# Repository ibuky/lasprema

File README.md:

# Avion
An wing-like 53-key keyboard inspired by Atreus.

### Features
- has 53 keys.
- is column-staggered.
- Supports Kailh choc and Cherry MX and its compatibles.
- has a central display spot for an artisan keycap.

[More information is available here.](https://www.taneyats.com/entry/lets-see-my-avion)(Japanese)

### Beta Version
This project still have lots to be completed.

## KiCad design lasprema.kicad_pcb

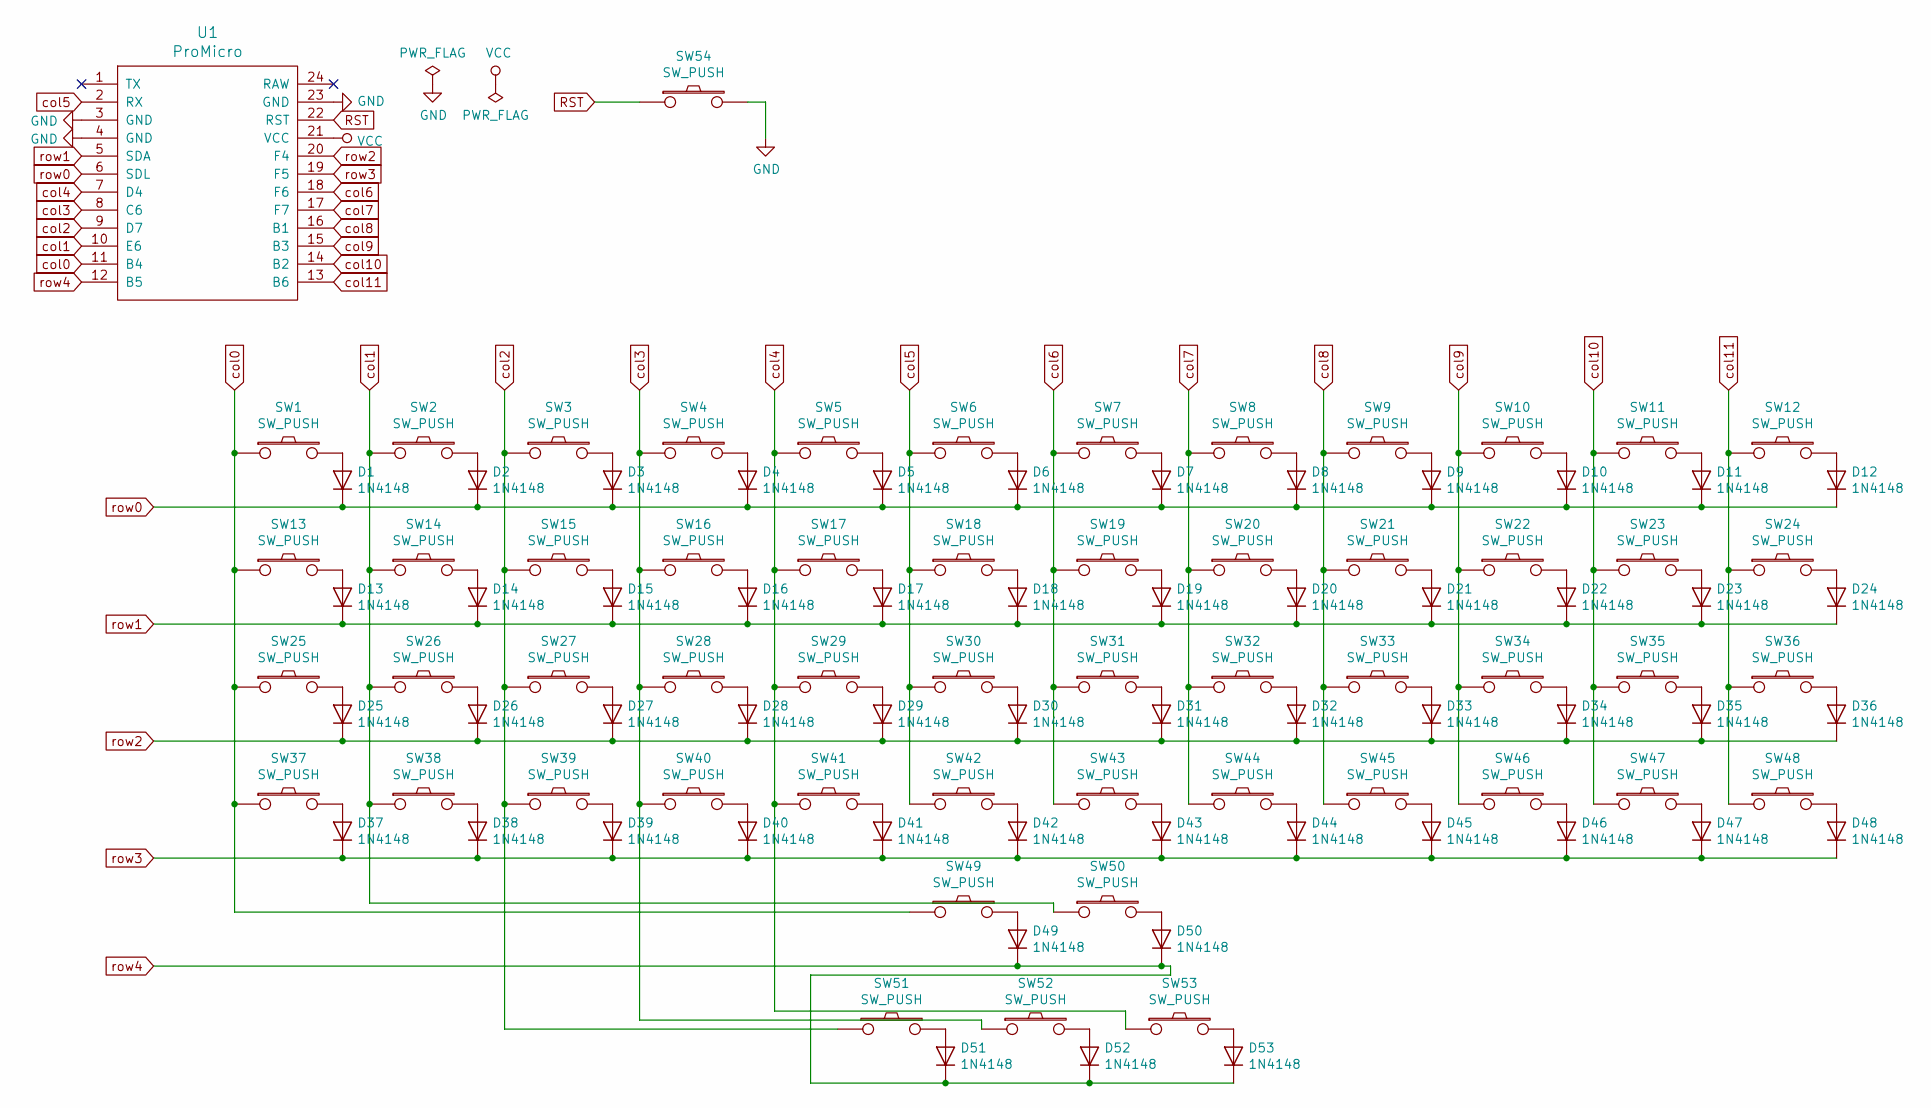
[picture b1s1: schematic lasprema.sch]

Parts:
D1, D2, D3, D4, D5, D6, D7, D8, D9, D10, D11, D12, D13, D14, D15, D16, D17, D18, D19, D20, D21, D22, D23, D24, D25, D26, D27, D28, D29, D30, D31, D32, D33, D34, D35, D36, D37, D38, D39, D40, D41, D42, D43, D44, D45, D46, D47, D48, D49, D50, D51, D52, D53: 1N4148; D_DO-35_SOD27_P7.62mm_Horizontal
SW1, SW2, SW3, SW4, SW5, SW6, SW7, SW8, SW9, SW10, SW11, SW12, SW13, SW14, SW15, SW16, SW17, SW18, SW19, SW20, SW21, SW22, SW23, SW24, SW25, SW26, SW27, SW28, SW29, SW30, SW31, SW32, SW33, SW34, SW35, SW36, SW37, SW38, SW39, SW40, SW41, SW42, SW43, SW44, SW45, SW46, SW47, SW48, SW49, SW50, SW51, SW52, SW53: SW_PUSH; lopro_compatible
SW54: SW_PUSH; SW_PUSH_6mm
U1: ProMicro

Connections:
GND: SW54.2, U1.3 (GND), U1.4 (GND), U1.23 (GND)
unnamed: D1.2 (A), SW1.2
unnamed: D2.2 (A), SW2.2
unnamed: D3.2 (A), SW3.2
unnamed: D4.2 (A), SW4.2
unnamed: D5.2 (A), SW5.2
unnamed: D6.2 (A), SW6.2
unnamed: D7.2 (A), SW7.2
unnamed: D8.2 (A), SW8.2
unnamed: D9.2 (A), SW9.2
unnamed: D10.2 (A), SW10.2
unnamed: D11.2 (A), SW11.2
unnamed: D12.2 (A), SW12.2
unnamed: D13.2 (A), SW13.2
unnamed: D14.2 (A), SW14.2
unnamed: D15.2 (A), SW15.2
unnamed: D16.2 (A), SW16.2
unnamed: D17.2 (A), SW17.2
unnamed: D18.2 (A), SW18.2
unnamed: D19.2 (A), SW19.2
unnamed: D20.2 (A), SW20.2
unnamed: D21.2 (A), SW21.2
unnamed: D22.2 (A), SW22.2
unnamed: D23.2 (A), SW23.2
unnamed: D24.2 (A), SW24.2
unnamed: D25.2 (A), SW25.2
unnamed: D26.2 (A), SW26.2
unnamed: D27.2 (A), SW27.2
unnamed: D28.2 (A), SW28.2
unnamed: D29.2 (A), SW29.2
unnamed: D30.2 (A), SW30.2
unnamed: D31.2 (A), SW31.2
unnamed: D32.2 (A), SW32.2
unnamed: D33.2 (A), SW33.2
unnamed: D34.2 (A), SW34.2
unnamed: D35.2 (A), SW35.2
unnamed: D36.2 (A), SW36.2
unnamed: D37.2 (A), SW37.2
unnamed: D38.2 (A), SW38.2
unnamed: D39.2 (A), SW39.2
unnamed: D40.2 (A), SW40.2
unnamed: D41.2 (A), SW41.2
unnamed: D42.2 (A), SW42.2
unnamed: D43.2 (A), SW43.2
unnamed: D44.2 (A), SW44.2
unnamed: D45.2 (A), SW45.2
unnamed: D46.2 (A), SW46.2
unnamed: D47.2 (A), SW47.2
unnamed: D48.2 (A), SW48.2
unnamed: D49.2 (A), SW49.2
unnamed: D50.2 (A), SW50.2
unnamed: D51.2 (A), SW51.2
unnamed: D52.2 (A), SW52.2
unnamed: D53.2 (A), SW53.2
RST: SW54.1, U1.22 (RST)
VCC: U1.21 (VCC)
col0: SW1.1, SW13.1, SW25.1, SW37.1, SW49.1, U1.11 (B4)
col1: SW2.1, SW14.1, SW26.1, SW38.1, SW50.1, U1.10 (E6)
col2: SW3.1, SW15.1, SW27.1, SW39.1, SW51.1, U1.9 (D7)
col3: SW4.1, SW16.1, SW28.1, SW40.1, SW52.1, U1.8 (C6)
col4: SW5.1, SW17.1, SW29.1, SW41.1, SW53.1, U1.7 (D4)
col5: SW6.1, SW18.1, SW30.1, SW42.1, U1.2 (RX)
col6: SW7.1, SW19.1, SW31.1, SW43.1, U1.18 (F6)
col7: SW8.1, SW20.1, SW32.1, SW44.1, U1.17 (F7)
col8: SW9.1, SW21.1, SW33.1, SW45.1, U1.16 (B1)
col9: SW10.1, SW22.1, SW34.1, SW46.1, U1.15 (B3)
col10: SW11.1, SW23.1, SW35.1, SW47.1, U1.14 (B2)
col11: SW12.1, SW24.1, SW36.1, SW48.1, U1.13 (B6)
row0: D1.1 (K), D2.1 (K), D3.1 (K), D4.1 (K), D5.1 (K), D6.1 (K), D7.1 (K), D8.1 (K), D9.1 (K), D10.1 (K), D11.1 (K), D12.1 (K), U1.6 (SDL)
row1: D13.1 (K), D14.1 (K), D15.1 (K), D16.1 (K), D17.1 (K), D18.1 (K), D19.1 (K), D20.1 (K), D21.1 (K), D22.1 (K), D23.1 (K), D24.1 (K), U1.5 (SDA)
row2: D25.1 (K), D26.1 (K), D27.1 (K), D28.1 (K), D29.1 (K), D30.1 (K), D31.1 (K), D32.1 (K), D33.1 (K), D34.1 (K), D35.1 (K), D36.1 (K), U1.20 (F4)
row3: D37.1 (K), D38.1 (K), D39.1 (K), D40.1 (K), D41.1 (K), D42.1 (K), D43.1 (K), D44.1 (K), D45.1 (K), D46.1 (K), D47.1 (K), D48.1 (K), U1.19 (F5)
row4: D49.1 (K), D50.1 (K), D51.1 (K), D52.1 (K), D53.1 (K), U1.12 (B5)

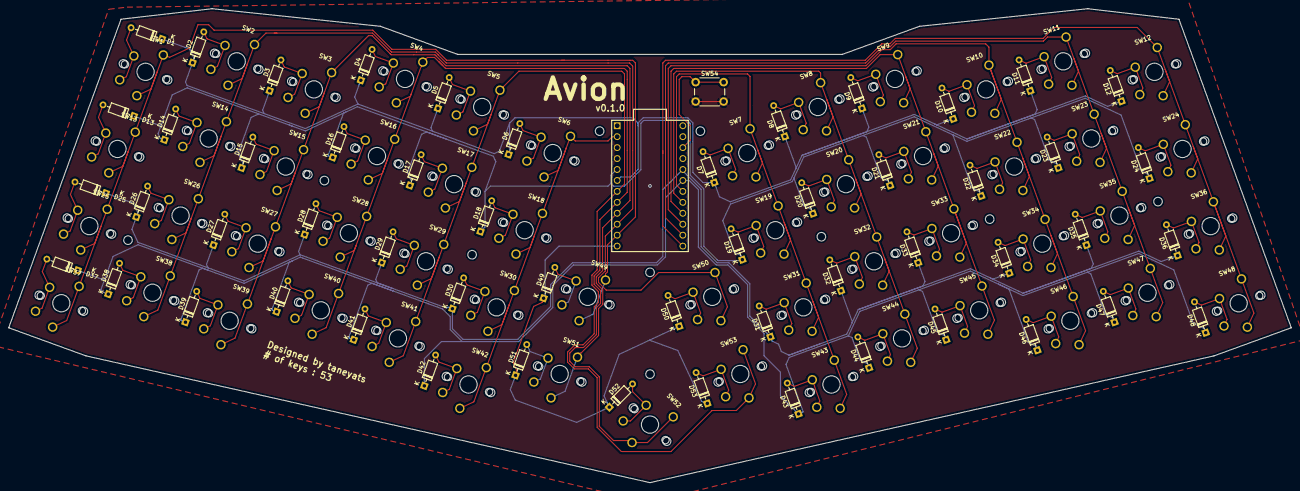
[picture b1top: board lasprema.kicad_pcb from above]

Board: 2 copper layers, 297.6 x 110.0 mm, 118 parts (0 on the bottom side), 72 nets.

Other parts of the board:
HOLE: screw_hole_2mm
HOLE#2, HOLE#3, HOLE#4, HOLE#5, HOLE#6, HOLE#7, HOLE#8, HOLE#9, HOLE#10: screw_hole_2mm

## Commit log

2019-05-23 init commit (after 1st publish)
2019-05-30 add case & confirm work perfect
2019-06-04 clean up files
2019-06-04 add readme
